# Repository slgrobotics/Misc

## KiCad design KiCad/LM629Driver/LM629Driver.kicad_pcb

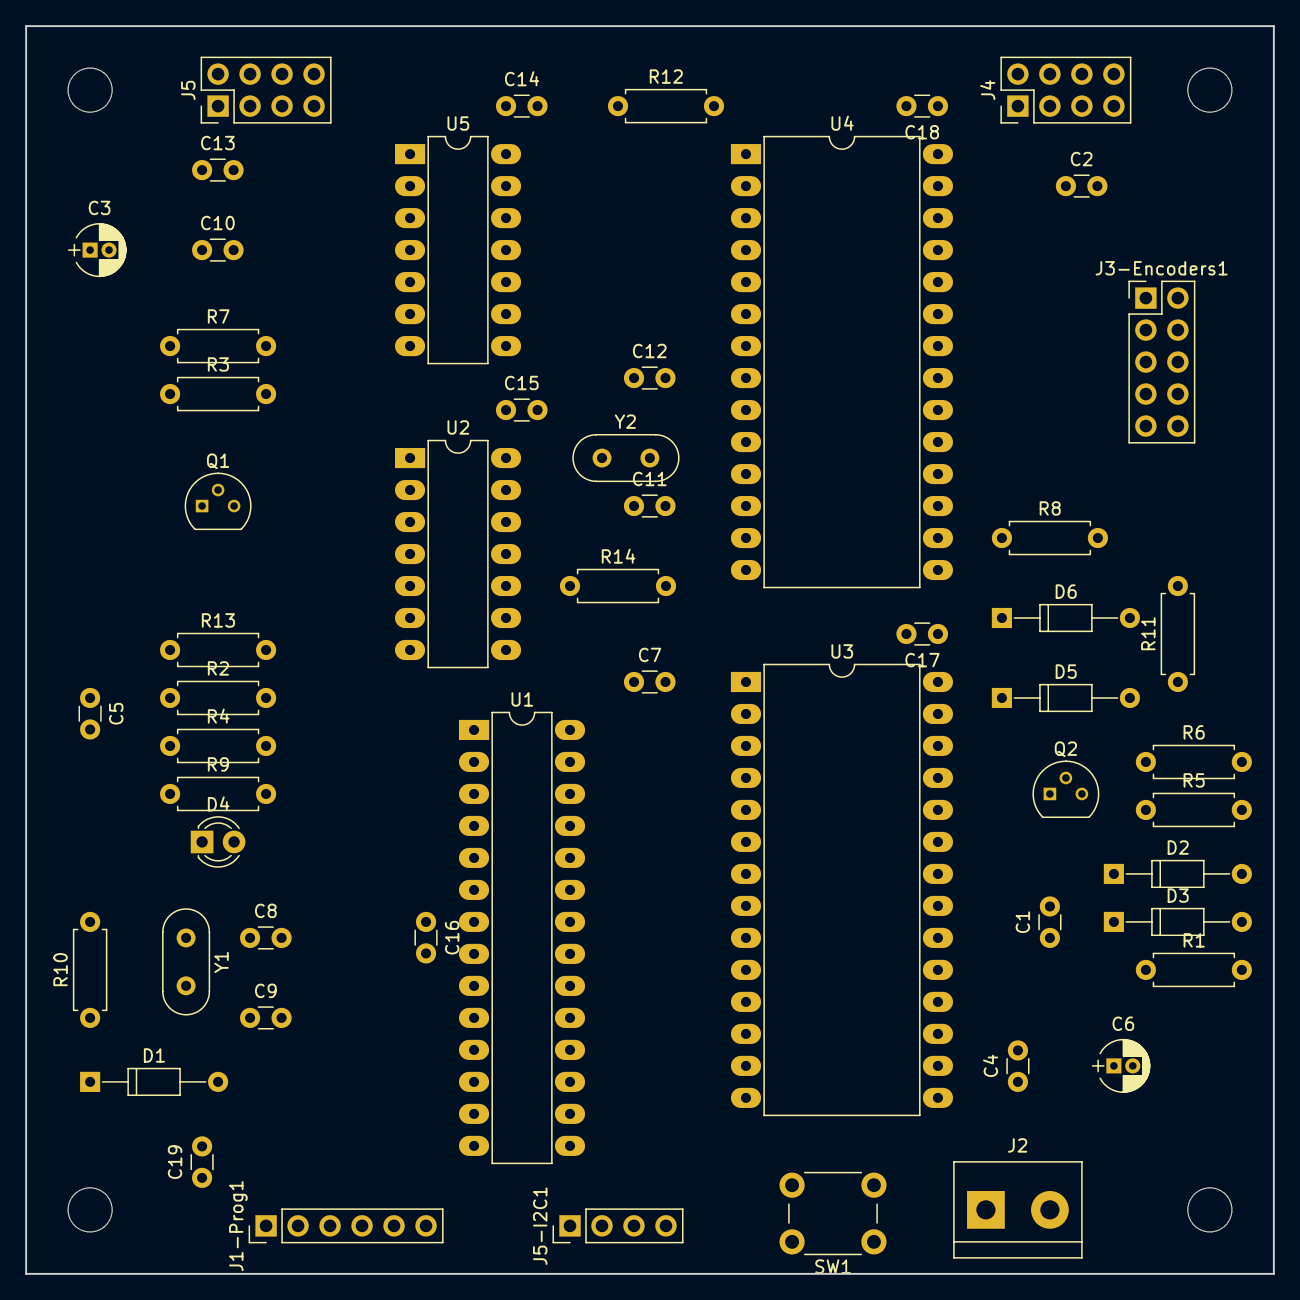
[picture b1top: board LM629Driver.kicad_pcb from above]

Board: 4 copper layers, 99.1 x 99.1 mm, 55 parts (0 on the bottom side), 57 nets, no tracks yet.

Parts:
C1, C2, C4, C5, C7, C10, C13: 0.1uF; C_Disc_D3.0mm_W1.6mm_P2.50mm
C3, C6: 22uF; CP_Radial_D4.0mm_P1.50mm
C8, C9, C12: 22pF; C_Disc_D3.0mm_W1.6mm_P2.50mm
C11: 68pF; C_Disc_D3.0mm_W1.6mm_P2.50mm
C14, C15, C16, C17, C18, C19: 10nF; C_Disc_D3.0mm_W1.6mm_P2.50mm
D1: 1N5817; D_DO-35_SOD27_P10.16mm_Horizontal
D2, D3, D5, D6: 1N60P; D_DO-35_SOD27_P10.16mm_Horizontal
D4: LED; LED_D3.0mm
J1-Prog1: Pin_Header_Straight_1x06_Pitch2.54mm
J2: bornier2
J3-Encoders1: Pin_Header_Straight_2x05_Pitch2.54mm
J4, J5: Pin_Header_Straight_2x04_Pitch2.54mm
J5-I2C1: Pin_Header_Straight_1x04_Pitch2.54mm
Q1: 2N3906; TO-92_Molded_Narrow
Q2: 2N3904; TO-92_Molded_Narrow
R1, R4, R5, R11: 10K; R_Axial_DIN0207_L6.3mm_D2.5mm_P7.62mm_Horizontal
R2: 22K; R_Axial_DIN0207_L6.3mm_D2.5mm_P7.62mm_Horizontal
R3, R6: 2K; R_Axial_DIN0207_L6.3mm_D2.5mm_P7.62mm_Horizontal
R7, R8, R9: 1K; R_Axial_DIN0207_L6.3mm_D2.5mm_P7.62mm_Horizontal
R10: 1M; R_Axial_DIN0207_L6.3mm_D2.5mm_P7.62mm_Horizontal
R12, R13: R; R_Axial_DIN0207_L6.3mm_D2.5mm_P7.62mm_Horizontal
R14: 10M; R_Axial_DIN0207_L6.3mm_D2.5mm_P7.62mm_Horizontal
SW1: Reset; SW_PUSH_6mm
U1: ATMEGA328P-PU; DIP-28_W7.62mm_LongPads
U2: 74HC04; DIP-14_W7.62mm_LongPads
U3, U4: LM629; DIP-28_W15.24mm_LongPads
U5: 74HCT00; DIP-14_W7.62mm_LongPads
Y1: 16MHz; Crystal_HC52-8mm_Vertical
Y2: 8MHz; Crystal_HC52-8mm_Vertical

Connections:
+5V: C2.1, C3.1, C4.1, C6.1, C10.2, C13.2, C14.1, C15.1, C16.1, C17.1, C18.1, C19.1, D1.1, J2.2, J3-Encoders1.7, J3-Encoders1.8, J4.5, J4.6, J5.5, J5.6, J5-I2C1.3, Q1.1, R1.1, R2.2, R3.1, R8.1, R11.2, R12.1, R13.1, U1.7, U1.20, U2.14, U3.28, U4.28, U5.14
GND: C1.2, C2.2, C3.2, C4.2, C6.2, C7.2, C8.1, C9.1, C10.1, C11.2, C13.1, C14.2, C15.2, C16.2, C17.2, C18.2, C19.2, D4.1, J1-Prog1.5, J1-Prog1.6, J2.1, J3-Encoders1.9, J3-Encoders1.10, J4.7, J4.8, J5.7, J5.8, J5-I2C1.4, Q2.1, R6.2, R7.2, SW1.1, U1.8, U1.22, U2.7, U3.14, U4.14, U5.7
unnamed: C1.1, D2.1
unnamed: C5.1, R2.1, SW1.2, U1.1
unnamed: C5.2, J1-Prog1.1
unnamed: C7.1, U1.21
unnamed: C8.2, R10.2, U1.9, Y1.1
unnamed: C9.2, R10.1, U1.10, Y1.2
unnamed: C11.1, R14.2, U2.5, Y2.1
unnamed: C12.1, R14.1, U2.6, U2.13
unnamed: C12.2, Y2.2
unnamed: D1.2, J1-Prog1.4
unnamed: D2.2, D3.2, R1.2, U3.27, U4.27
unnamed: D3.1, U1.24
unnamed: D4.2, R9.2
unnamed: D5.1, U3.17
unnamed: D5.2, D6.2, R11.1, U1.4
unnamed: D6.1, U4.17
unnamed: J1-Prog1.2, U1.3
unnamed: J1-Prog1.3, U1.2
unnamed: J3-Encoders1.1, R13.2, U3.1
unnamed: J3-Encoders1.2, R12.2, U4.1
unnamed: J3-Encoders1.3, U3.2
unnamed: J3-Encoders1.4, U4.2
unnamed: J3-Encoders1.5, U3.3
unnamed: J3-Encoders1.6, U4.3
unnamed: J4.1, U2.9, U3.18, U5.5
unnamed: J4.2, U2.11, U4.18, U5.13
unnamed: J4.3, U3.19, U5.1, U5.4
unnamed: J4.4, U4.19, U5.9, U5.12
unnamed: J5-I2C1.1, U1.27
unnamed: J5-I2C1.2, U1.28
unnamed: J5.1, U5.6
unnamed: J5.2, U5.11
unnamed: J5.3, U5.3
unnamed: J5.4, U5.8
unnamed: Q1.2, R3.2, R4.1
unnamed: Q1.3, R7.1, U2.1
unnamed: Q2.2, R5.2, R6.1
unnamed: Q2.3, R8.2, U3.15, U4.15
unnamed: R4.2, R5.1, U1.26
unnamed: R9.1, U1.19
unnamed: U1.5, U2.3, U3.12
unnamed: U1.6, U3.16, U4.16
unnamed: U1.11, U3.4, U4.4
unnamed: U1.12, U3.5, U4.5
unnamed: U1.13, U3.6, U4.6
unnamed: U1.14, U3.7, U4.7
unnamed: U1.15, U3.8, U4.8
unnamed: U1.16, U3.9, U4.9
unnamed: U1.17, U3.10, U4.10
unnamed: U1.18, U3.11, U4.11
unnamed: U2.2, U3.13, U4.13
unnamed: U2.4, U4.12
unnamed: U2.8, U5.2
unnamed: U2.10, U5.10
unnamed: U2.12, U3.26, U4.26

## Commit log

2017-06-09 Selected Arduino projects
    Disclaimer: mostly somebody else's code possibly modified by me. No
    warranties of any kind.
2020-05-01 added test for BT_2 H-Bridge and WiperMotorServo code
2020-05-07 Update WiperMotorServo.ino
    Added switch between RC and Pot control, tested on first two "final" servos
2020-05-09 Added schematics and pictures of BigMotorServo
    Added schematics and pictures of BigMotorServo
2020-06-16 Works all right on R/C Lawn Mower
2020-08-21 Former Big Balancer converted to Lawnmower staging/debugging platform. First cut.
    Working code - former Big Balancer converted to Lawnmower staging/debugging platform.
2020-08-21 KiCad files for LM629 Motor Controller chip PCB
    KiCad files for LM629 Motor Controller chip PCB. Sample code in Arduino Sketchbook and library
2020-09-30 DraggerRC introduced and merged to Dragger
    DraggerRC - a variation of Dragger, controlled by R/C two channels only, ready for first test (Lawnmower project)
    Dragger - Updated by merging good changes from DraggerRC - specifically fixing jerking on overfilling R/Ldistance at 32K
2021-02-09 New motors, switched L/R encoders, double pwm_R/L
    New motors, switched L/R encoders, double pwm_R/L to avoid rounding issues
2021-02-09 Create uarts_test_holybro.py
    Test Holybro telemetry radios pair using RPi Pico
2021-02-11 Added joystick control
    Added joystick control, works fine. Joystick connected by wire to A0, A1
2021-02-11 added deadzone to joystick
2021-02-21 OpenSCAD projects
    My own OpenScad designs
2021-09-15 RPi Pico over SmartLab ReCon 6.0 - first cut
    Works well with joystick.
2021-09-17 Added Pixy camera
    Added Pixy camera (first edition) via PixyToSerial.ino on Arduino Leonardo. Chases the ball all right.
2021-09-28 All Raspberry Pico and ReCon 6 code
    Added Raspberry Pico and ReCon 6 code - tests and tries. Work in progress
2021-10-08 Added R/C PPM Receiver for PX4 Lawnmower project
    Added R/C PPM Receiver for PX4 Lawnmower project. Runs on Teensy 3.2 and supplies data to Raspberry Pi via I2C
2022-05-26 Tested latest working code for small balancer
2022-06-09 Added camera-related Raspberry Pi code
2022-06-09 Added missing files
2022-06-09 added more from W:\Sergei\ROS\RPi\Projects\Backup-Jessie
2022-07-23 Working test for Jetson hoverboard, RioRand controllers
2022-07-23 Added comments
2022-07-25 Works on UNO and ESP8266 in SPI or I2C mode
2022-07-26 Comments added
2022-07-26 PWM test uses shift register for dir, stop, brake
2022-07-26 Added ESP8266 interrupts test
2022-07-27 First cut of ESP8266 Balancer, using Shifty in PWM
2022-07-29 WIP - assigned Dx pins to Voyager circuits correctly
2022-08-05 Updated to latest versions and proper Voyager hoverboard wiring
2022-08-08 Removed Docs folders, added BalancerDfrFOC
2022-08-08 Added Android Balancer controller code from 2017
2022-08-10 Compiles and runs on Nexus5 phone under latest Android Studio
2022-08-11 Balancer Controller works fine
2022-08-13 Works well with Android app, reworked to use SoftTimer library
2022-08-15 Works fine with Android app
2022-08-17 Works well, PIDs adjusted
2022-08-17 Refactored for SoftTimer, works fine
2022-10-29 Working on audio FFT
2022-10-29 Refactored into tabs, switched to digital mic, adjusted display
2022-10-29 Works fine on RPi Pico
    Spectrum display of audio signal on 128x64 OLED
2022-11-11 Checked in latest version
2022-11-11 Checked in latest version from my Sketchbook
2022-12-10 Adjusted RC Input for PCA 9685 very precise 1500us midpoint, added DEADZONE_RC
2022-12-10 Working fine with MAX98357A I2S Audio DAC/Amplifier
2023-02-09 Added Turtlebot Gyro for Create 1 base
2023-02-15 Update ParkingSensorI2C.ino
    See schematics at https://photos.app.goo.gl/WsqkA4XpYSLrVDX59
2023-02-16 Update ParkingSensor.ino
    Added schematics link at https://photos.app.goo.gl/WsqkA4XpYSLrVDX59
    *
2023-02-16 Added PluckyWheelsROS - just copied from PluckyWheels
    To start ROS2 conversion based on Articulated Robotics code
2023-02-18 Works fine with Articulated Robotics code
2023-02-19 Update PluckyComm.ino
    Replaced comm output with sprintf(), works fine with RPi
2023-02-20 Update PluckyComm.ino
    Added response for empty string
2023-02-20 Improved Comm
    Using sprintf() and sending command char back
2023-02-21 Introduced READ_GPS and READ_HEALTH
    works fine
2023-02-21 Create GPSKitchenSink.ino
    To support PluckyWheelsROS
2023-03-01 Adjusted for measured wheel rotation speeds
    // desiredSpeed* is in the range -100...100 - it has a meaning of "percent of max possible speed".
    // it must be scaled if ticks/sec or rad/sec or m/sec is desired.
    For Plucky full wheel rotation at full power takes 3.8 seconds. So, with R_wheel = 0.192m max speed is:
    - 0.317 m/sec
    - 1.65 rad/sec
    - 660 encoder ticks/sec
2023-04-01 Create MPU9250GyroCompassShorty.ino
    That's legacy IMU for Plucky
2024-06-23 emulate the PCA9685 Raspberry Pi Hat using Teensy 4.0 microcontroller
    Working code, all good on Lawnmower
2024-06-25 Added DraggerROS code
2024-07-27 Old toy Abrams tank, radio replaced with this.
2024-10-11 Adjusted DraggerROS for battery monitoring
    Included PID_v1 library, as the PID_v1_bc doesn't work well (wheels rotate after stop)
2024-11-30 Another pass on Arduino - PluckyWheelsROS and DraggerROS
2024-11-30 DraggerROS, PluckyWheelsROS updated
2024-11-30 PluckyWheelsROS, DraggerROS auto-formatted
2024-12-01 Minor cleanup PluckyWheelsROS and DraggerROS
2025-01-28 Adjusted while making DraggerROS talk to ParkingSensorI2C
2025-01-31 Improvements for I2C handling - Parking sensor, Dragger, Plucky and test
2025-02-16 Calibrated current sensor on Dragger
2025-02-17 Added current sensor for Plucky, calibrated and working
2025-02-27 Reworked Dragger Motors to IBT-2 H-Bridge after burning the DBH-1 controllers
2025-03-01 Using EMA for Dragger wheels
2025-07-29 LD2410/LD2412 sketches added
2025-08-18 Added DFRobot Detect Gesture example and Cannon OpenScad files
2025-10-03 Initial check-in - WheelsRos_Raspberry Pi Pico
2025-10-04 Ifdefs: HAS_ENCODERS, USE_PIDS, works with joystick
2025-10-06 WheelsROS_Pico: Excess in diff PWM calculation
2025-10-06 Update Motors.ino
    Nicer definitions for servos trimming
2025-10-08 Added comments for clarity
2025-10-13 Create FOC_open_loop_velocity_example.ino
    Works with either wheel of Segway Ninebot miniPRO, simpleFOC driver board - https://github.com/ChenDMLSY/FOC-SimpleFOC-MotorDriveDevelopmentBoard/tree/main
2025-10-14 Create FOC_open_loop_miniPRO.ino
    Works with both wheels miniPRO
2025-10-14 Initial check-in
2025-10-14 Auto formatted FOC velocity control example
2025-10-14 Update FOC_open_loop_velocity_example.ino
    Minor edits
2025-10-15 Created Teensy 4.0 FOC test and PID vel control sketches
2025-10-16 Added Python script to analyze logs produced by Teensy Serial
2025-10-16 Initial check-in: copied from FOC_auto_test_Teensy_40_chatgpt
2025-10-16 Update FOC_auto_test_Teensy_40_cs_chatgpt.ino
    auto-formatted, works with current sensing
2025-10-17 Adding documentation for my simpleFOC projects
2025-10-17 Revise README with new pointers and project links
    Updated README.md to include additional resources and project links.
2025-10-18 Update link for Segway Ninebot miniPRO project
